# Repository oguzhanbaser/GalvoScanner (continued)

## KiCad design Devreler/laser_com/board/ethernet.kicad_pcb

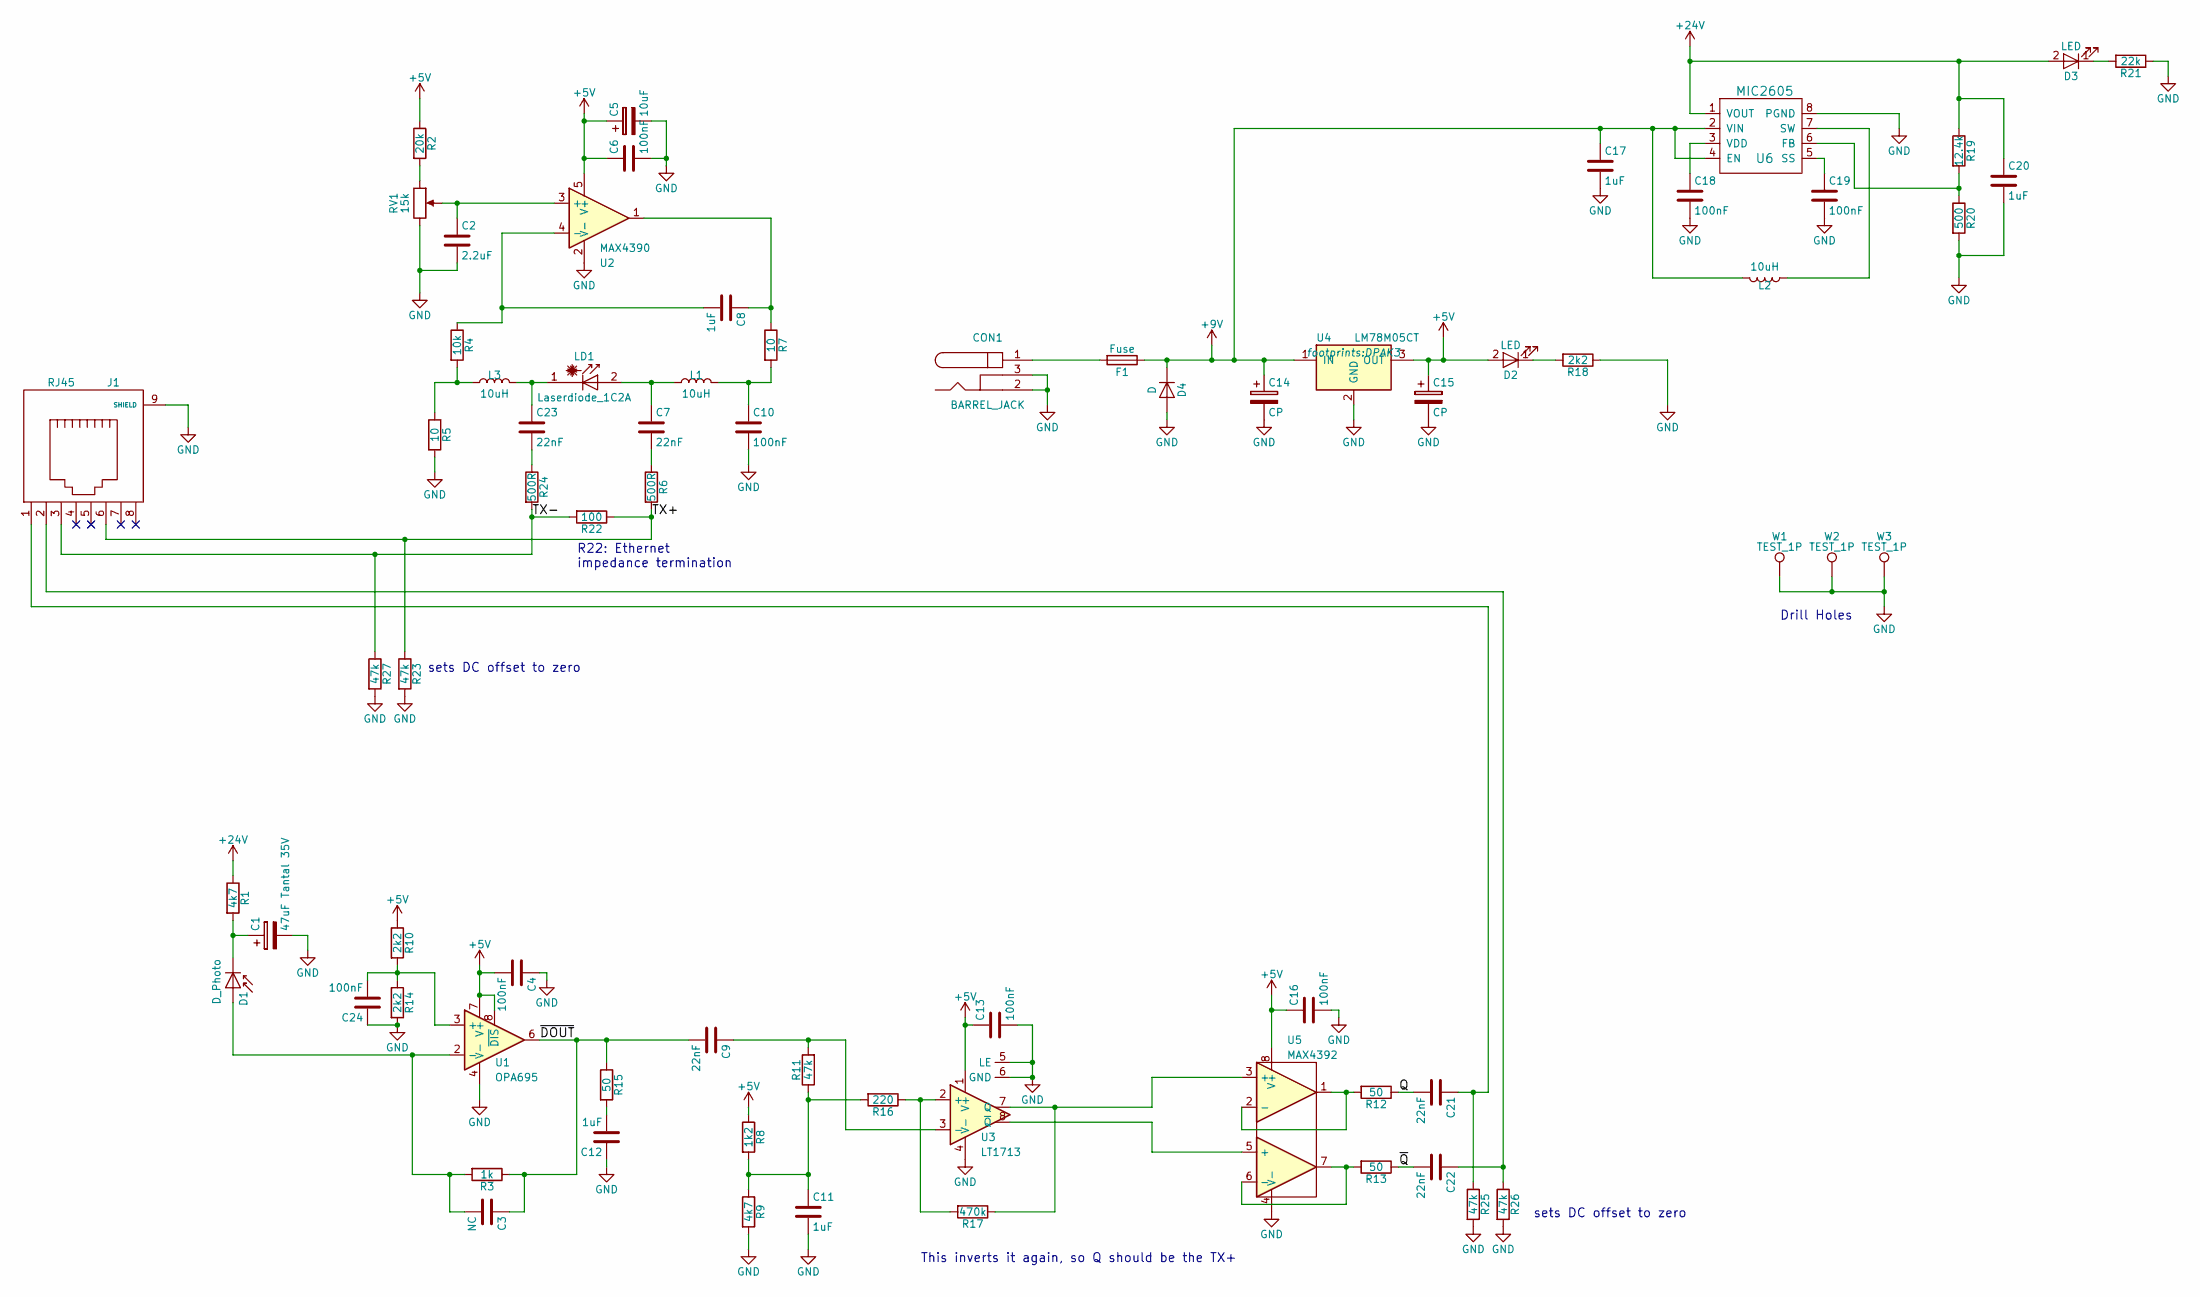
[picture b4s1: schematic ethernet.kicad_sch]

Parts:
C1: 47uF Tantal 35V; CP_Tantalum_Case-V_EIA-7343-20_Reflow
C2: 2.2uF; C_0603_HandSoldering
C3: NC; C_0603_HandSoldering
C4, C6, C10, C13, C16, C18, C19, C24: 100nF; C_0603_HandSoldering
C5: 10uF; CP_Elec_4x5.8
C7, C9, C21, C22, C23: 22nF; C_0603_HandSoldering
C8, C11, C12, C17, C20: 1uF; C_0603_HandSoldering
C14, C15: CP; CP_Elec_4x5.8
CON1: BARREL_JACK
D1: D_Photo; LED_D3.0mm_Horicontal_O2.54mm
D2, D3: LED; R_0603_HandSoldering
D4: D; C_0603_HandSoldering
F1: Fuse; Fuseholder5x20_horiz_SemiClosed_Casing10x25mm
J1: RJ45; RJ45_AMPH
L1, L2, L3: 10uH; C_1210_HandSoldering
LD1: Laserdiode_1C2A; laserdiode_6mm
R1, R9: 4k7; R_0603_HandSoldering
R2: 20k; R_0603_HandSoldering
R3: 1k; R_0603_HandSoldering
R4: 10k; R_0603_HandSoldering
R5, R7: 10; R_0603_HandSoldering
R6, R24: 500R; R_0603_HandSoldering
R8: 1k2; R_0603_HandSoldering
R10, R14, R18: 2k2; R_0603_HandSoldering
R11, R23, R25, R26, R27: 47k; R_0603_HandSoldering
R12, R13, R15: 50; R_0603_HandSoldering
R16: 220; R_0603_HandSoldering
R17: 470k; R_0603_HandSoldering
R19: 12.4k; R_0603_HandSoldering
R20: 500; R_0603_HandSoldering
R21: 22k; R_0603_HandSoldering
R22: 100; R_0603_HandSoldering
RV1: 15k; TC33k
U1: OPA695; SOIC-8_3.9x4.9mm_Pitch1.27mm
U2: MAX4390; SOT-23-5
U3: LT1713; MSOP-8_3x3mm_Pitch0.65mm
U4: LM78M05CT; DPAK3
U5: MAX4392; umax8
U6: MIC2605; MLF2x2
W1, W2, W3: TEST_1P; 3mm_drill

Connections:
+5V: C4.2, C5.1, C6.1, C13.1, C15.1, C16.1, D2.2 (A), R2.1, R8.1, R10.1, U1.7 (V+), U1.8 (~DIS), U2.5 (V+), U3.1 (V+), U4.3 (OUT), U5.8 (V+)
+9V: C14.1, C17.1, D4.1 (K), F1.1, L2.1, U4.1 (IN), U6.2 (VIN), U6.4 (EN)
+24V: C20.1, D3.2 (A), R1.1, R19.1, U6.1 (VOUT)
/Q: C21.2, R12.1
/TX+: J1.6, R6.2, R22.1, R23.1
/TX-: J1.3, R22.2, R24.2, R27.1
/~DOUT: C3.1, C9.2, R3.1, R15.1, U1.6
/~Q: C22.2, R13.1
GND: C1.2, C2.2, C4.1, C5.2, C6.2, C10.2, C11.2, C12.1, C13.2, C14.2, C15.2, C16.2, C17.2, C18.2, C19.2, C20.2, C24.1, CON1.2, CON1.3, D4.2 (A), J1.9 (SHIELD), R5.2, R9.2, R14.2, R18.1, R20.2, R21.1, R23.2, R25.2, R26.2, R27.2, RV1.3, U1.4 (V-), U2.2 (V-), U3.4 (V-), U3.5 (LE), U3.6 (GND), U4.2 (GND), U5.4 (V-), U6.8 (PGND), W1.1, W2.1, W3.1
unnamed: C1.1, D1.1 (K), R1.2
unnamed: C2.1, RV1.2, U2.3 (+)
unnamed: C3.2, D1.2 (A), R3.2, U1.2 (-)
unnamed: C7.1, L1.2, LD1.2 (A)
unnamed: C7.2, R6.1
unnamed: C8.1, R7.1, U2.1
unnamed: C8.2, R4.1, U2.4 (-)
unnamed: C9.1, R11.2, U3.3 (-)
unnamed: C10.1, L1.1, R7.2
unnamed: C11.1, R8.2, R9.1, R11.1, R16.2
unnamed: C12.2, R15.2
unnamed: C18.1, U6.3 (VDD)
unnamed: C19.1, U6.5 (SS)
unnamed: C21.1, J1.1, R25.1
unnamed: C22.1, J1.2, R26.1
unnamed: C23.1, L3.1, LD1.1 (K)
unnamed: C23.2, R24.1
unnamed: C24.2, R10.2, R14.1, U1.3 (+)
unnamed: CON1.1, F1.2
unnamed: D2.1 (K), R18.2
unnamed: D3.1 (K), R21.2
unnamed: L2.2, U6.7 (SW)
unnamed: L3.2, R4.2, R5.1
unnamed: R2.2, RV1.1
unnamed: R12.2, U5.1, U5.2 (-)
unnamed: R13.2, U5.6 (-), U5.7
unnamed: R16.1, R17.2, U3.2 (+)
unnamed: R17.1, U3.7 (Q), U5.3 (+)
unnamed: R19.2, R20.1, U6.6 (FB)
unnamed: U3.8 (~Q), U5.5 (+)

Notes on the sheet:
Drill Holes
This inverts it again, so Q should be the TX+
R22: Ethernet impedance termination
sets DC offset to zero

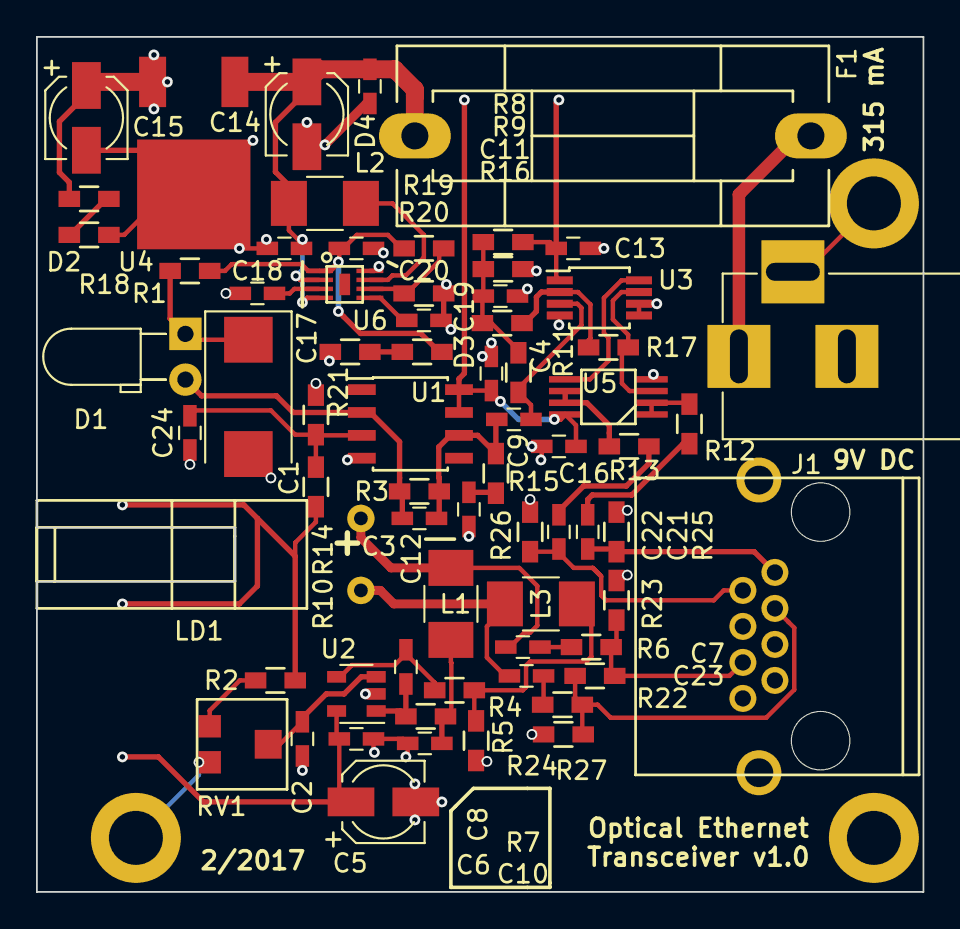
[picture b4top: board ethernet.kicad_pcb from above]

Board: 2 copper layers, 49.2 x 47.5 mm, 72 parts (0 on the bottom side), 39 nets.

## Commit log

2025-10-02 repo yu oluşturmak için ilk commit - şematik çizimler eklendi -- referans devreler -- esp devresi - yazılım dosyaları eklendi -- gazeobo simülasyon -- esp yazılımları -- python kontrol yazılımı
2025-10-02 Readme dosyası eklendi
2025-10-17 - Accelstepper kullanılıyor - düşük hata ile adımlama yapılıyor
2025-10-24 - ana yazılımda yeni hesaplama eklendi - test için drv8825 yazılımı eklendi
2025-11-30 - görünt,ü işleme yazılımları eklendi
2025-12-07 - mydetector düzenleniyor - main dosyası hazırlanmaya başlandı - uzaktan yönetim eklenecek
2025-12-11 - mydetector sınıfı tamamlandı - lazer ve led tespiti tek sınıf içerisinde - tam işlenvsel çalışmıyor - test resmi eklendi -
2025-12-11 - sınıf güncellendi, ilk testler için hazır - tekil yazılımlar çalışıyor ve renkleri json olarak kaydediyorlar
2025-12-12 - eşikler geliştirildi - çözünülük büyükken led ler tespit edilmiyor.
2025-12-13 - esp yazılımı güncellendi - lazer takip algoritması ve seri haberleşme eklendi - ilk testler yapıldı - eksen hareketi 0 da bitmiyor - renk tespiti ışığa ve arka plan rengine çok duyarlı
2025-12-14 - komutlara geri besleme eklendi
2025-12-20 esp yazılımı ve python yazılımı güncellendi
    - esp yazılımı için yeni kart yazılımı embed klasörünün altına eklendi
    - python yazılımında eksnlerin G kod yerleri değiştirildi
    - python yazılımı ile lazer ortlama yapabiliyor.
2025-12-27 raspi software
2025-12-27 Bazı dosyalar silindi
2025-12-27 tekrar deneme
2026-01-01 - develop branch i düzenlendi
2026-01-01 - flowchart eklendi
2026-01-02 web arayüz eklendi
2026-01-02 - web panel düzenlendi ve görüntü akışı hızlandırıldı - işlenne görüntü çözünürlüğü 640x480
2026-01-02 - web kameraya doğrudan bağlantı sisteme entegre edildi - görüntü işleme algoritmaları hızlandırıldı
2026-01-07 -app_state bağlantısı sınıfa çevirldi -seri haberleşme testleri yapıldı - motor arayüzden kontrol edilebiliyor - bazı seri haberleşme sorunlaro düzeltildi -esp yazılımda Serial1 düzeltildi
2026-01-24 - önyüzde bazı düzenlemer yapıldı - hassas takip işlemi için başlık eklendi - adc den okuma yaparak hassas hareket işlemleri eklenecek
2026-02-07 yeşil lazer ve ledler karışıyor
2026-02-12 yeşil lazer ve mavi LED karışma sorunu giderildi - inpaint algoritmasının radius u arttırıldı
2026-03-05 - inpainting alanı performans sebei ile küçültüldü - piksel çevrelerine aynı piksellerdek ekleme yapılarak led ve lazer tespiti yapılıyor.
2026-03-08 hassas takip işlemi tamamlandı
2026-03-08 hassas takip işlemleri tamamlandı
2026-03-28 -test yazılımları eklendi - hassas takibin adım hızları düşürüldü
